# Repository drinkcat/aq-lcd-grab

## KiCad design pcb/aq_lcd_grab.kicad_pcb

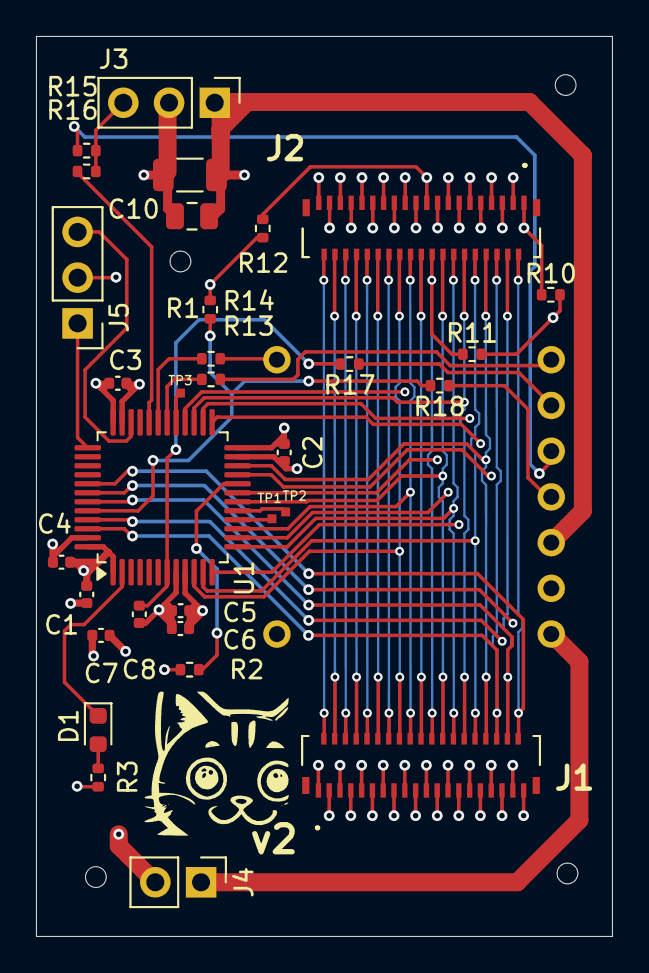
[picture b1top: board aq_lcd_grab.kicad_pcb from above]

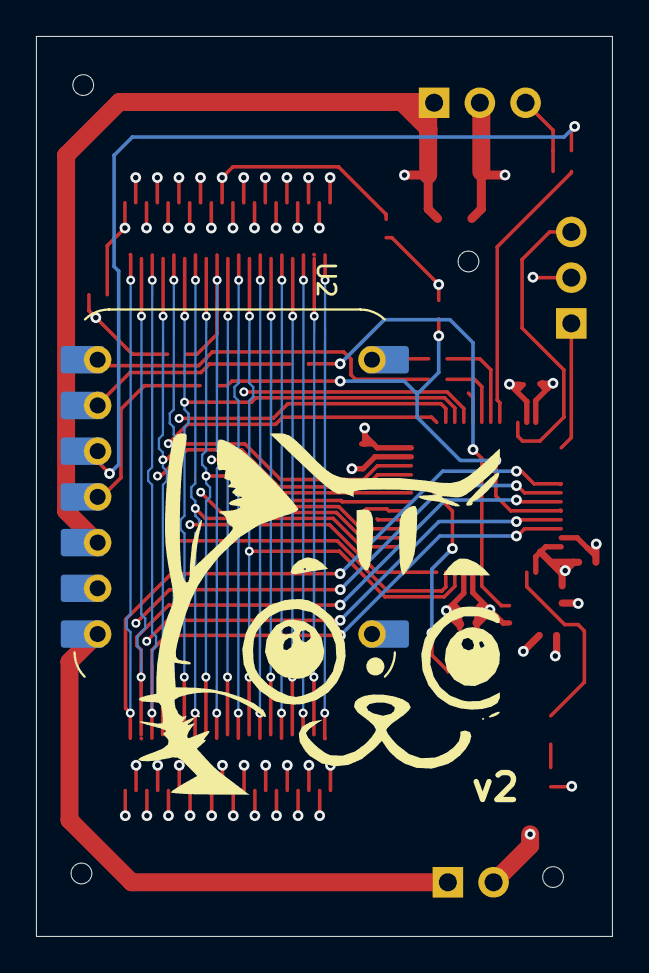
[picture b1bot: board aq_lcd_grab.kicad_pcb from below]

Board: 4 copper layers, 32.0 x 50.0 mm, 39 parts (2 on the bottom side), 61 nets.

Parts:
C1, C2, C3, C4, C5, C8: 100n; C_0402_1005Metric
C6: 1u; C_0402_1005Metric
C7: 4.7u; C_0402_1005Metric
C10: 22u; C_0805_2012Metric
C11: 100u; C_1206_3216Metric
D1: KT-0603R; LED_0603_1608Metric
H1, H2, H3, H4: ToolingHole; ToolingHole_1.152mm
J1, J2: FH26W-39S-0.3SHW(60); FH26W39S03SHW60
J3: Conn_01x03_Socket; PinHeader_1x03_P2.54mm_Vertical
J4: Conn_01x02_Socket; PinHeader_1x02_P2.54mm_Vertical
J5: Conn_01x03_Pin; PinHeader_1x03_P2.54mm_Vertical
R1, R2: 10k; R_0402_1005Metric
R3: 1k; R_0402_1005Metric
R10, R11, R12, R13, R14, R15, R16, R17, R18: 0; R_0402_1005Metric
TP1, TP2, TP3: TestPoint; TestPoint_Pad_0.5x0.5mm
U1: STM32F103C8T6; LQFP-48_7x7mm_P0.5mm
U2: Conn_01x14; XIAO-ESP32-C6-DIP
v2: LOGO; logo-8mm
v2#2: LOGO; logo-2cm

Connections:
+3V3: C1.1, C2.1, C3.1, C4.1, C5.1, C6.1, C7.1, C10.1, C11.1, J3.1, R3.1, U1.1, U1.9, U1.24, U1.36, U1.48, U2.12
+5V: J4.1, U2.14
BOOT0: R1.1, R18.2, U1.44
BOOT0_ESP: R18.1, U2.11
BOOT1: R2.1, U1.20
CS: J1.18, J2.22, U1.15
DB0: J1.38, J2.2, U1.41
DB1: J1.37, J2.3, U1.42
DB2: J1.36, J2.4, U1.43
DB3: J1.35, J2.5, U1.45
DB4: J1.34, J2.6, U1.46
DB5: J1.33, J2.7, U1.21
DB6: J1.32, J2.8, U1.22
DB7: J1.31, J2.9, U1.25
DB8: J1.30, J2.10, U1.11
DB9: J1.29, J2.11, U1.26
DB10: J1.28, J2.12, U1.27
DB11: J1.27, J2.13, U1.12
DB12: J1.26, J2.14, U1.13
DB13: J1.25, J2.15, U1.14
DB14: J1.24, J2.16, U1.18
DB15: J1.23, J2.17, U1.19
DC: J1.17, J2.23, U1.28
GND: C1.2, C2.2, C3.2, C4.2, C5.2, C6.2, C7.2, C8.2, C10.2, C11.2, J3.2, J4.2, J5.2, R1.2, R2.2, R10.2, R11.2, R12.2, U1.8, U1.23, U1.35, U1.47, U2.13
GND_1: J1.39, J2.1, R10.1
GND_18: J1.22, J2.18, R11.1
GND_19: J1.21, J2.19, R12.1
LED_STATUS: D1.1, U1.2
unnamed: D1.2, R3.2
NRST: C8.1, R17.2, U1.7
NRST_ESP: R17.1, U2.9
P20_RD: J1.20, J2.20
P21: J1.19, J2.21
P25: J1.15, J2.25
P26: J1.14, J2.26
P27: J1.13, J2.27
P28: J1.12, J2.28
P29: J1.11, J2.29
P30: J1.10, J2.30
P31: J1.9, J2.31
P32: J1.8, J2.32
P34: J1.6, J2.34
P38: J1.2, J2.38
P39: J1.1, J2.39
PA6: TP1.1, U1.16
PA7: TP2.1, U1.17
PA8: TP3.1, U1.29
PIC32_RESET: J3.3, R15.2, R16.2
PIC32_RST_ESP: R15.1, U2.10
PIC32_RST_STM: R16.1, U1.32
SWCLK: J5.1, U1.37
SWDIO: J5.3, U1.34
UART_ESP_RX: R13.2, U2.8
UART_ESP_TX: R14.2, U2.7
UART_STM_RX: R14.1, U1.31
UART_STM_TX: R13.1, U1.30
VCC_33: J1.7, J2.33
VCC_35: J1.5, J2.35
VCC_36: J1.4, J2.36
VCC_37: J1.3, J2.37
WR: J1.16, J2.24, U1.10

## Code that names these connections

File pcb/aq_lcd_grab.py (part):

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          footprint="Connector_PinHeader_2.54mm:PinHeader_1x03_P2.54mm_Vertical",
          ref="J3",
          tag="J3_MAINBOARD_POWER")
# PIC32_RESET is the shared net at J3. ESP32 GPIO20 and STM32 PA11 each
# drive it through a 0 Ω jumper (open-drain; target pull-up on main board).
# Breaking a jumper isolates that driver without cutting the other path.
PIC32_RESET = Net("PIC32_RESET")
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
# PA11 (pin 32): second open-drain driver for PIC32 reset. Wired through
# 0 Ω jumper R16 onto PIC32_RESET; break R16 to isolate STM32 from the line.
U1[32] += PIC32_RST_STM    # PA11

# --- SWD header (3-pin) ------------------------------------------------
# Pinout mirrors the prior board's convention: pin 1 SWCLK, pin 2 GND,
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# side from an external USB-UART probe without the other side pulling
# on the line. Place the jumpers near the STM32 (short stubs on the
# probe-friendly ESP32 side).
UART_STM_TX = Net("UART_STM_TX")        # STM32 TX (PA9) -> jumper -> ESP32 RX
UART_STM_RX = Net("UART_STM_RX")        # STM32 RX (PA10) <- jumper <- ESP32 TX
UART_ESP_RX = Net("UART_ESP_RX")        # ESP32-side of TX line
UART_ESP_TX = Net("UART_ESP_TX")        # ESP32-side of RX line
U1[30] += UART_STM_TX                   # PA9
U1[31] += UART_STM_RX                   # PA10

R_UART_TX = R("0", "R13", "R_UART_TX_BREAK")
R_UART_TX[1] += UART_STM_TX; R_UART_TX[2] += UART_ESP_RX
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             tag="D1_LED_STATUS")
R_LED[1] += P3V3
R_LED[2] += D_LED[2]      # anode (pin 2)
D_LED[1] += LED_STATUS    # cathode (pin 1) -> PC13
U1[2] += LED_STATUS


# =============================================================================
# Bring-up test points on STM32 free pins
# PA6/PA7/PA8 are free with no AF conflicts in our configuration.
# Bring-up serial console uses SWO via the SWD probe (Q14), not a
# dedicated UART pad cluster.
TEST_POINTS = [
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U2[14] += P5V

# USART1 to STM32 (ROM bootloader + runtime; up to 115200+)
U2[7] += UART_ESP_TX    # ESP32 TX -> 0 Ω -> STM32 RX (PA10)
U2[8] += UART_ESP_RX    # ESP32 RX <- 0 Ω <- STM32 TX (PA9)

# Reset / boot control — each line broken by a 0 Ω jumper so the ESP32
# can be isolated during bring-up without cutting NRST/BOOT0 from the SWD
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R_NRST_BREAK[1]  += NRST_ESP;  R_NRST_BREAK[2]  += NRST
R_BOOT0_BREAK = R("0", "R18", "R_BOOT0_BREAK")
R_BOOT0_BREAK[1] += BOOT0_ESP; R_BOOT0_BREAK[2] += BOOT0
U2[9]  += NRST_ESP   # GPIO19 — open-drain (NRST has internal pull-up)
U2[10] += PIC32_RST_ESP  # GPIO20 — open-drain; target provides the pull-up
U2[11] += BOOT0_ESP  # GPIO18 — push-pull, drive HIGH to enter bootloader

# Bulk decoupling near Xiao 3V3 pad to absorb WiFi TX peaks locally so
# the target 3V3 rail doesn't see them as transients (pcb_spec.md Q6/Q7).
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
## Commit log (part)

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2026-05-15 Initial commit, add notes from Claude
2026-05-15 Add Pico 2 W hello world firmware
    Embassy on RP2350, USB CDC serial logger ticking once per 500 ms.
    Verified end-to-end via /dev/ttyACM0.
    Toolchain note in firmware/README.md: must install elf2uf2-rs from
    git (not crates.io v2.2.0, which silently produces RP2040-family UF2s
    that the RP2350 boot ROM rejects).
2026-05-15 Prune unused firmware deps
    embassy-usb, embassy-futures, static_cell are not referenced in
    main.rs — embassy-usb-logger pulls in embassy-usb transitively.
    cargo build --release, cargo fmt --check, and
    cargo clippy --release -- -D warnings all clean.
2026-05-15 Add PIO+DMA capture proof-of-concept
    pio_capture.rs sets up PIO0 SM0 with a 3-instruction program that
    waits for WR (GPIO 18) low->high, then samples {CS, DC, DB15..DB0}
    into a 18-bit FIFO word. DMA channel drains the FIFO into a static
    buffer. main.rs awaits one full 4096-word buffer per loop and dumps
    the first 32 decoded samples over USB CDC.
    Verified booting on the Pico 2 W: USB CDC up, "waiting for samples"
2026-05-15 Switch flash runner from elf2uf2-rs to picotool
    `picotool load -u -v -x -t elf` flashes, verifies, and executes the
    ELF in one command over the BOOTSEL USB interface — no mass-storage
    mount, no family-ID footgun, no fork-of-fork install. Verified
    end-to-end: cargo run --release boots the firmware directly from
    BOOTSEL with progress bars and an "OK" line.
    Still need to enter BOOTSEL manually (hold button + replug) since
2026-05-15 Eliminate BOOTSEL dance via picotool reset interface
    Adds a vendor-specific USB interface (class 0xff / subclass 0x00 /
    protocol 0x01) with a control-request handler that calls the boot ROM's
    `reset_to_usb_boot()` when picotool sends `bRequest=0x01` to that
    interface. Combined with embassy-usb's CDC ACM logger, the device now
    runs three concurrent futures: USB device pump, logger pump, and the
    PIO capture loop.
2026-05-15 PoC captures real ILI9488/ST7796 traffic from the target
    Two changes that, together, turned the first live capture from "only
    the top two bits ever toggle" into recognizable bus traffic:
    1. PIO shift_in direction: Right -> Left.
    With shift_right, autopush at threshold=18 leaves the sampled bits
    in the upper 18 bits of the pushed u32 (bits 14..31), not at the
    bottom. Our decode read `sample & 0xFFFF`, so it was reading
2026-05-15 Add host/ Rust+egui viewer for target capture stream
    Reads the firmware's text dump from /dev/ttyACM0 (or a replay file),
    decodes the 18-bit packed samples back into bus events, splits them into
    transactions on DC transitions, and replays SET_COLUMN_ADDRESS /
    SET_ROW_ADDRESS / MEMORY_WRITE into a 320x480 RGB565 framebuffer
    displayed in an egui window. A side panel lists recent transactions
    with their ILI9488 command names and a hex preview of the data.
2026-05-15 Switch firmware->host stream from text dumps to binary frames
    The hex-dump approach was bursting one 4096-sample capture every ~8
    seconds, with the firmware spending ~5 s formatting + sending ~230 KB
    of ASCII per dump and a 3 s sleep between captures. On a 1-Hz burst
    cadence that was an 88% loss rate.
    Now:
    - Firmware decodes samples into transactions on-Pico (cmd byte + up
2026-05-31 PCB: Sent for fabrication -- v1
